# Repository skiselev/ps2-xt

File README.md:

# ps2-xt
PS/2 to XT Keyboard Converter

## Overview

The PS/2 to XT project is yet another PCB design for the [AT2XT keyboard converter](https://forum.vcfed.org/index.php?threads/at2xt-keyboard-converter.26861/) developed by [Vintage Computer Federation](https://vcfed.org/) community.

It allows connecting a PS/2 keyboard to an IBM PC, IBM XT, or compatibles. An AT keyboard with an additional passive AT to PS/2 adapter, or a USB keyboard that also supports AT protocol using passive USB to PS/2 adapter, can be also used with this converter.

It was designed for several reasons:
1. Initially I couldn't find the original PCB design.
2. The original design is somewhat bulky.
3. I wanted a nice 3D printed case to go with it.
4. I wanted an easy to build and service design, with through hole components.
5. A friend asked for one...

## Hardware Documentation

### Schematic and PCB Layout

* [Schematic - Version 1.0](https://github.com/skiselev/ps2-xt/blob/main/KiCad/ps2-xt-1.0-schematic.pdf)
* [PCB Layout - Version 1.0](https://github.com/skiselev/ps2-xt/blob/main/KiCad/ps2-xt-1.0-board.pdf)
* [3D printed case - Version 1.0](https://github.com/skiselev/ps2-xt/tree/main/printed)

### Assembly Instructions

1. Obtain all the parts necessary. Most parts can be purchased from Mouser. The PCB can be ordered from a PCB manufacturer of your choice using provided KiCad and Gerber files.
2. Gather tools and supplies: Soldering iron, small side cutters, needle nose pliers for forming component's leads, solder, solder wick, alcohol and lint free wipes for cleanup. You also will need a programmer to program the firmware into PIC12F629 microcontroller.
3. Start by soldering the D1 1N4148 diode. Bend the leads 90 degrees by holding each side of the diode with the pliers, and gently bending the pins down. When soldering the diode pay attention to the polarity. The black ring mark on the diode should match the white mark on the PCB silkscreen. Trim the leads using the cutters.
4. Solder R1-R3 resistors. Bend the leads 90 degrees down by gently bending them right next to the resistor's package using your fingers. Resistors don't have polarity, but note that R1 and R2 are 4.7k, while R3 is 47k. Trim the leads using the cutters.
5. Solder U1 socket. Pay attention to the socket's orientation. The notch indicating the first pin on the socket should match with the notch on the PCB silkscreen.
6. Solder SW1 switch.
7. Solder C1 capacitor. Pay attention to the polarity. The white stripe on the capacitor should match the white mark on the PCB silkscreen. Trim the leads using the cutters.
8. Solder J2 MiniDIN-6 / PS/2 connector.
9. Solder J1 DIN-5 / XT keyboard connector.
10. Check the soldering work. Clean the flux using some alcohol and wipes.
11. Program U1 PIC12F629 microcontroller and install it into the socket. Pay attention to its orientation.
12. If desired, print and assemble the 3D case using provided STL files.

### Bill of Materials

* [PS2-XT project on Mouser.com](https://www.mouser.com/Tools/Project/Share?AccessID=ace9059e87) - View and order all the components.
* [PS2-XT project on OSH Park](https://oshpark.com/shared_projects/D2kvqnaq) - View and order the PCB.

Component type     | Reference | Description                                 | Quantity | Possible sources and notes 
------------------ | --------- | ------------------------------------------- | -------- | --------------------------
PCB                |           | PS2-XT PCB - Version 1.0                    | 1        | Order from a PCB manufacturer of your choice using provided [Gerber](https://github.com/skiselev/ps2-xt/tree/main/gerber) or [KiCad](https://github.com/skiselev/ps2-xt/tree/main/KiCad) files
Integrated Circuit | U1        | PIC12F629 Microcontroller RTC, 8 pin DIP    | 1        | Mouser [579-PIC12F629IP](https://www.mouser.com/ProductDetail/579-PIC12F629IP)
IC Socket          | U2        | 8 pin DIP                                   | 1        | Mouser [737-ICS-308-T](https://www.mouser.com/ProductDetail/737-ICS-308-T)
Diode              | D1        | 1N4148                                      | 1        | Mouser [512-1N4148TA](https://www.mouser.com/ProductDetail/512-1N4148TA)
Capacitor          | C1        | 47 pF, 25V, electrolythic, 2 mm pitch       | 1        | Mouser [710-860040472001](https://www.mouser.com/ProductDetail/710-860040472001)
Resistor           | R1 - R2   | 4.7 kohm, 0.25 W, 1% tolerance, axial       | 2        | Mouser [603-MFR-25FRF52-4K7](https://www.mouser.com/ProductDetail/603-MFR-25FRF52-4K7)
Resistor           | R3        | 47 kohm, 0.25 W, 1% tolerance, axial        | 1        | Mouser [603-MFR-25FRF52-47K](https://www.mouser.com/ProductDetail/603-MFR-25FRF52-47K)
Connector          | J1        | DIN-5 socket                                | 1        | Mouser [806-KCDX-5S-S2](https://www.mouser.com/ProductDetail/806-KCDX-5S-S2)
Connector          | J2        | MiniDin-6 socket                            | 1        | Mouser [806-KMDGX-6S-BS](https://www.mouser.com/ProductDetail/806-KMDGX-6S-BS)
Switch             | SW1       | Slider SPDT switch                          | 1        | Mouser [179-SLW8645872ARAND](https://www.mouser.com/ProductDetail/179-SLW8645872ARAND)

## Additional Photos

### Complete PS/2 to XT in a Case

### Both Sides of the Assembled Boards

## Release Notes

### Changes

### Known Issues

* Version 1.0
  * No known issues

### Wishlist
* Use smaller footprint for the DIN-5. Reduce the PCB size.

## Red Tape

### Licensing

The hardware design itself, including schematic, PCB layout design, and 3D printed case design files are licensed under the strongly-reciprocal variant of [CERN Open Hardware Licence version 2](license-cern_ohl_s_v2.txt). Documentation, including this file, is licensed under the [Creative Commons Attribution-ShareAlike 4.0 International License](license-cc-by-sa-4.0.txt).

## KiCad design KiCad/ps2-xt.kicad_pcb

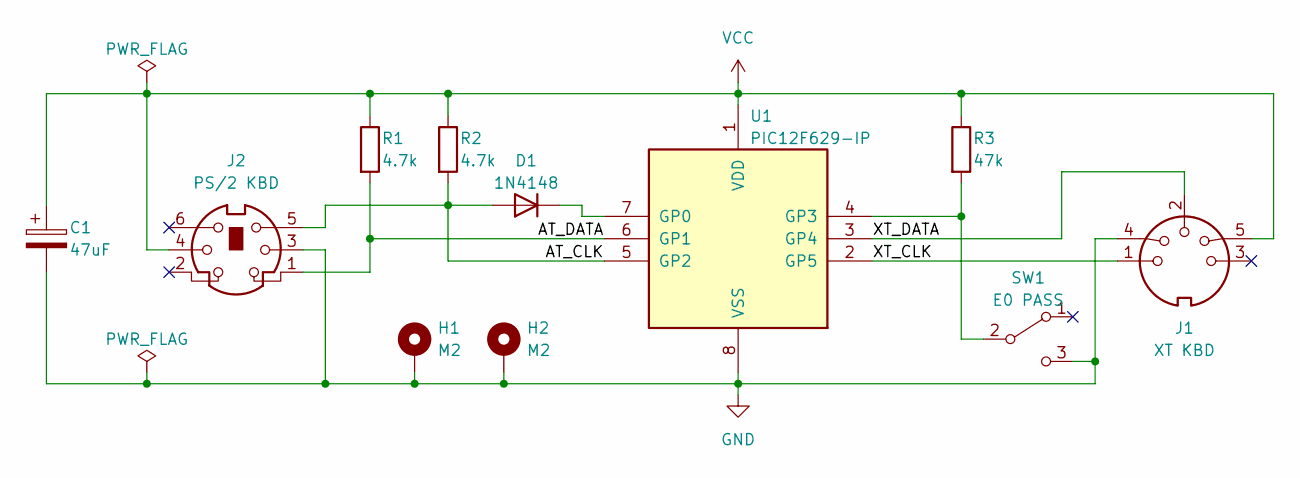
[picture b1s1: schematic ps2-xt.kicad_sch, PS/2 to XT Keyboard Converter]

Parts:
C1: 47uF; CP_Radial_D5.0mm_P2.00mm
D1: 1N4148; D_DO-35_SOD27_P7.62mm_Horizontal
H1, H2: M2; MountingHole_2.2mm_M2_Pad
J1: XT KBD; Conn_DIN_5pin
J2: PS/2 KBD; Conn_Mini_DIN_6pin
R1, R2: 4.7k; R_Axial_DIN0207_L6.3mm_D2.5mm_P7.62mm_Horizontal
R3: 47k; R_Axial_DIN0207_L6.3mm_D2.5mm_P7.62mm_Horizontal
SW1: E0 PASS; SW_CuK_OS102011MA1QN1_SPDT_Angled
U1: PIC12F629-IP; DIP-8_W7.62mm

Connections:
/AT_CLK: D1.2 (A), J2.5, R2.2, U1.5 (GP2)
/AT_DATA: J2.1, R1.2, U1.6 (GP1)
/XT_CLK: J1.1, U1.2 (GP5)
/XT_DATA: J1.2, U1.3 (GP4)
GND: C1.2, H1.1, H2.1, J1.0, J1.4, J1.~, J2.3, J2.~, SW1.3 (C), U1.8 (VSS)
unnamed: D1.1 (K), U1.7 (GP0)
unnamed: R3.2, SW1.2 (B), U1.4 (GP3)
VCC: C1.1, J1.5, J2.4, R1.1, R2.1, R3.1, U1.1 (VDD)

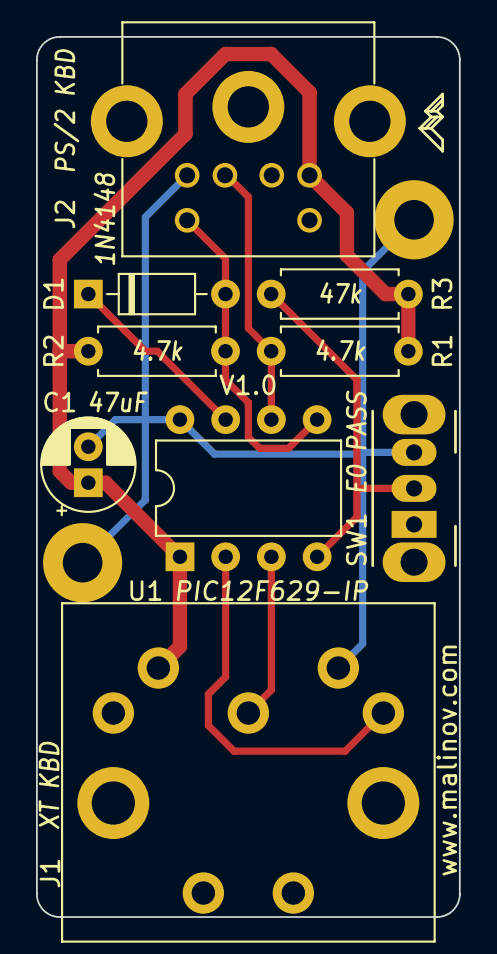
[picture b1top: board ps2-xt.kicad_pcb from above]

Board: 2 copper layers, 23.5 x 48.9 mm, 11 parts (0 on the bottom side), 8 nets.

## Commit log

2025-12-16 README: Initial content
2025-12-16 Add KiCad and Gerber files for V1.0
2025-12-16 README: Add links to the files in the repo
2025-12-16 Add license files
2026-01-22 Add 3D printed case
2026-01-22 Add photos
2026-01-22 README: Add pictures and 3D printed case link
2026-01-22 Add a photo of both sides of the board
2026-01-22 README: Add photo of both sides of the board
2026-01-22 README: Fix the link

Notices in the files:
KiCad/ps2-xt.kicad_pcb:
(C) 2025 Sergey Kiselev
(C) 2011 Charles P. Guzis
